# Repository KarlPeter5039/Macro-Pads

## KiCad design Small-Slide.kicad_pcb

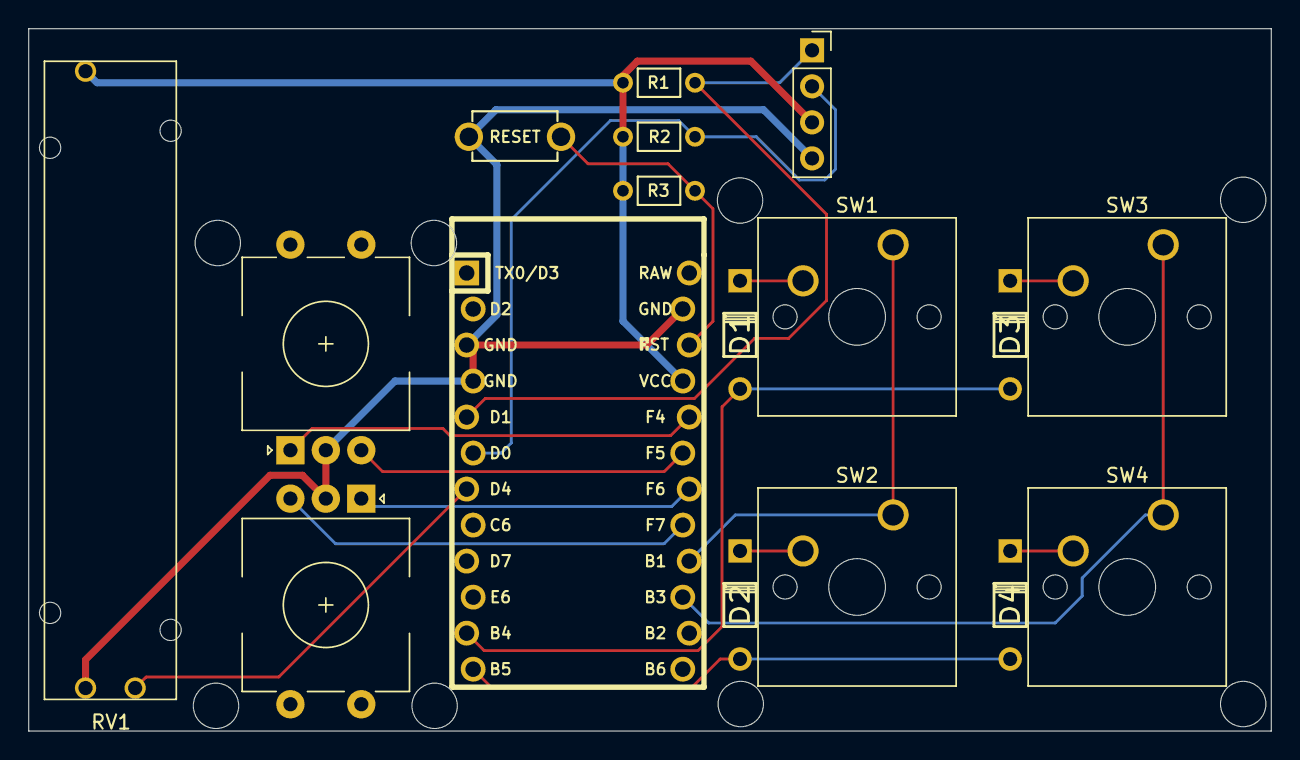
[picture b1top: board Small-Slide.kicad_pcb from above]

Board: 2 copper layers, 87.6 x 49.5 mm, 17 parts (0 on the bottom side), 18 nets.

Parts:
D1, D2, D3, D4: D_Small; Diode
P1: OLED; PinSocket_1x04_P2.54mm_Vertical
R1, R2, R3: R_US; RESISTOR
RV1: R_Potentiometer; potentiometer_slider_45mm
Rot2, Rot3: RotaryEncoder; RotaryEncoder_EC11
SW1, SW2, SW3, SW4: KEYSW; SW_Cherry_MX_1.00u_PCB
SW7: SW_Omron_B3FS; TACT_SWITCH_TVBP06
U1: ProMicro; ArduinoProMicro-ZigZag

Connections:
GND: P1.4, RV1.1, Rot2.C, Rot3.C, SW7.1, U1.3 (GND), U1.4 (GND), U1.23 (GND)
unnamed: D1.2 (A), SW1.2
unnamed: D2.2 (A), SW2.2
unnamed: D3.2 (A), SW3.2
unnamed: D4.2 (A), SW4.2
unnamed: R3.2, SW7.2, U1.22 (RST)
SCL: P1.2, R2.1, U1.6 (3/PD0)
SDA: P1.1, R1.2, U1.5 (2/PD1)
VCC: R1.1, R2.2, R3.1, RV1.3, U1.21 (VCC)
col0: SW1.1, SW2.1, U1.16 (15/PB1)
col1: SW3.1, SW4.1, U1.15 (14/PB3)
encA: RV1.2, U1.7 (4/PD4)
encC: Rot2.A, U1.20 (A3/PF4)
encD: Rot2.B, U1.19 (A2/PF5)
encE: Rot3.A, U1.18 (A1/PF6)
encF: Rot3.B, U1.17 (A0/PF7)
rowA: D1.1 (K), D3.1 (K), U1.11 (8/PB4)
rowB: D2.1 (K), D4.1 (K), U1.12 (9/PB5)
